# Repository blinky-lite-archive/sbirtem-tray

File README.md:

# SbirTem Thermal Imager
## .env file
`PROJECT=sbirtem`  
`DEVICETYPEA=sbirtem`  
`DEVICENAMEA=01`  
`MQTTCLIENTID=sbirtem-tray-01`  
`MQTTSERVERIP=`*your-MQTT-broker-URL*  
`MQTTUSERNAME=`*your-MQTT-broker-username*  
`MQTTPASSWORD=`*your-MQTT-broker-password*
`NODEREDCONFIGSECRET=`*another-choice*

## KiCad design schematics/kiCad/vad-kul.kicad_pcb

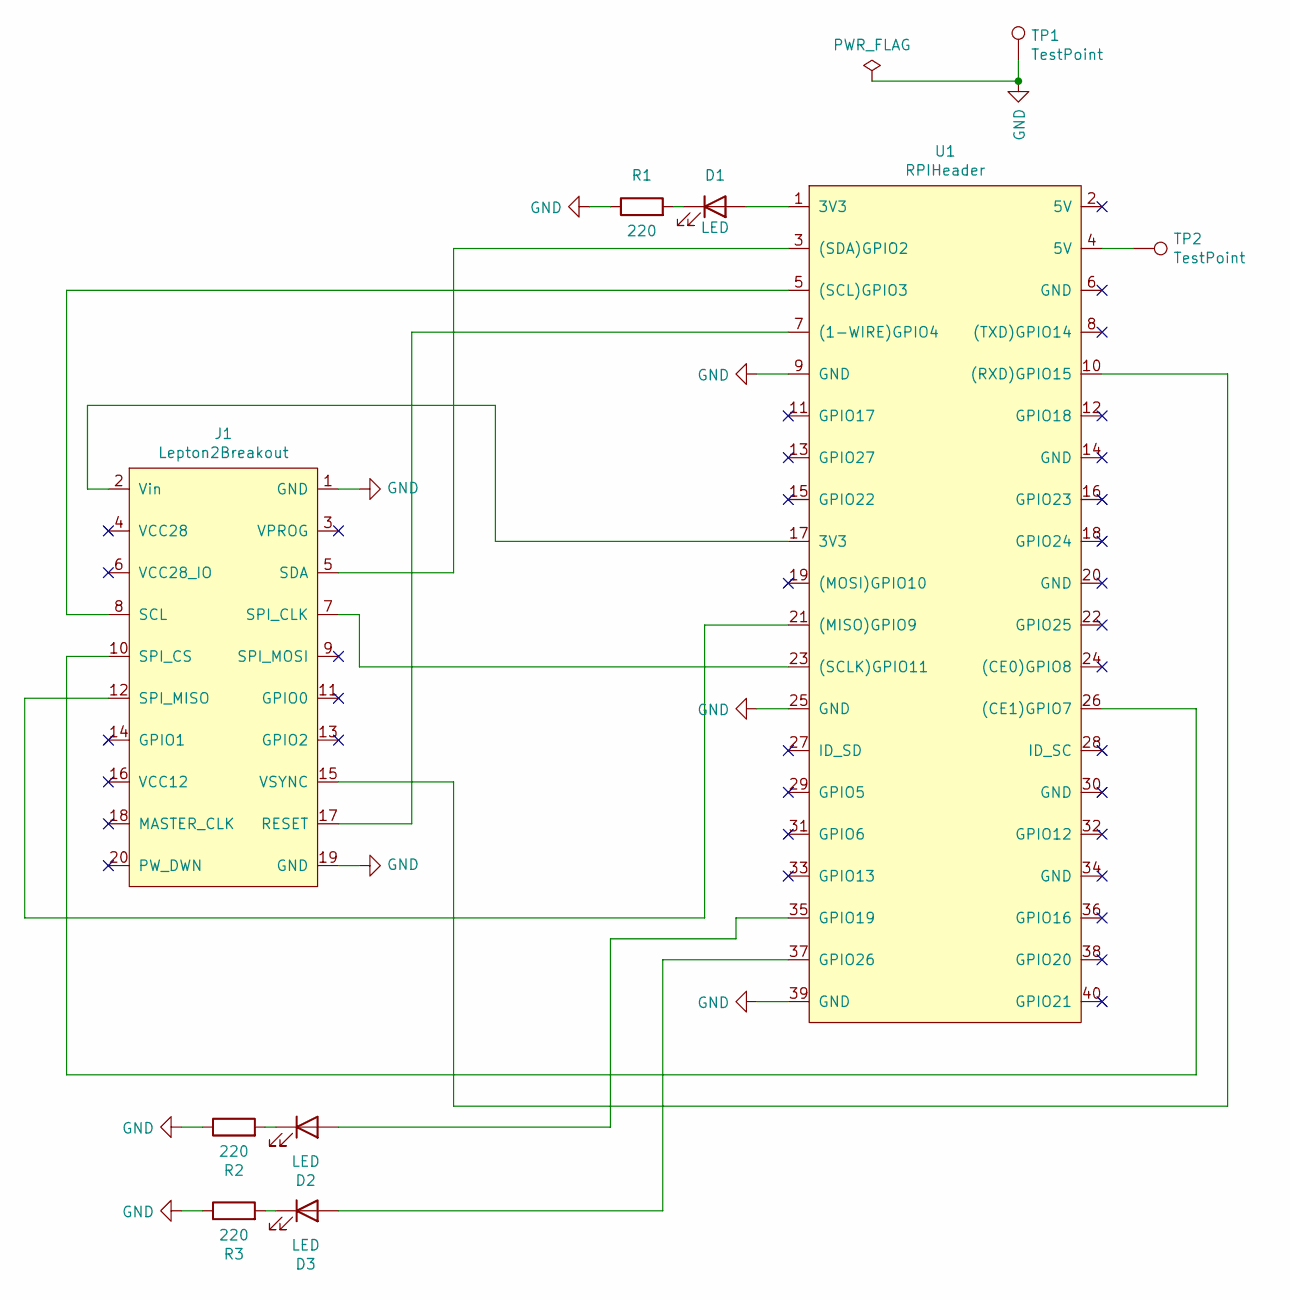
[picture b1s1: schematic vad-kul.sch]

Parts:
D1, D2, D3: LED; LED_D5.0mm
J1: Lepton2Breakout; Lepton2BO_RA
R1, R2, R3: 220; R_1206_3216Metric_Pad1.42x1.75mm_HandSolder
TP1, TP2: TestPoint; PinHeader_1x01_P2.54mm_Vertical
U1: RPIHeader; PinHeader_2x20_P2.54mm_Vertical

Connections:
GND: J1.1 (GND), J1.19 (GND), R1.1, R2.1, R3.1, TP1.1, U1.9 (GND), U1.25 (GND), U1.39 (GND)
unnamed: D1.1 (K), R1.2
unnamed: D1.2 (A), U1.1 (3V3)
unnamed: D2.1 (K), R2.2
unnamed: D2.2 (A), U1.35 (GPIO19)
unnamed: D3.1 (K), R3.2
unnamed: D3.2 (A), U1.37 (GPIO26)
unnamed: J1.2 (Vin), U1.17 (3V3)
unnamed: J1.5 (SDA), U1.3 ((SDA)GPIO2)
unnamed: J1.7 (SPI_CLK), U1.23 ((SCLK)GPIO11)
unnamed: J1.8 (SCL), U1.5 ((SCL)GPIO3)
unnamed: J1.10 (SPI_CS), U1.26 ((CE1)GPIO7)
unnamed: J1.12 (SPI_MISO), U1.21 ((MISO)GPIO9)
unnamed: J1.15 (VSYNC), U1.10 ((RXD)GPIO15)
unnamed: J1.17 (RESET), U1.7 ((1-WIRE)GPIO4)
unnamed: TP2.1, U1.4 (5V)

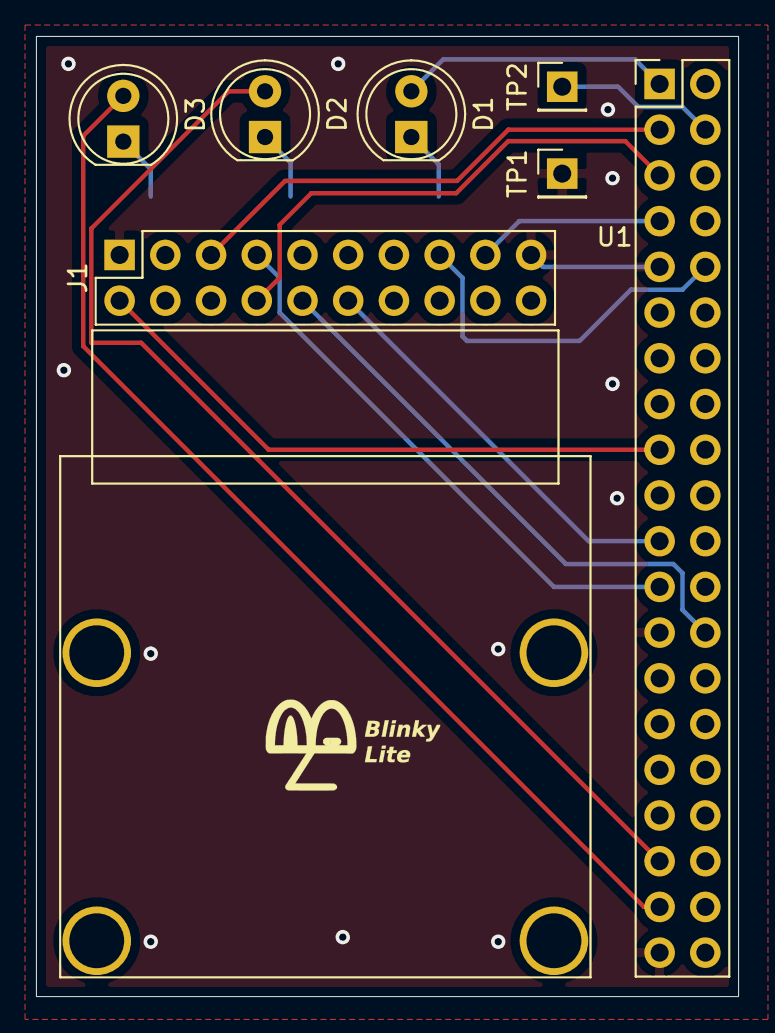
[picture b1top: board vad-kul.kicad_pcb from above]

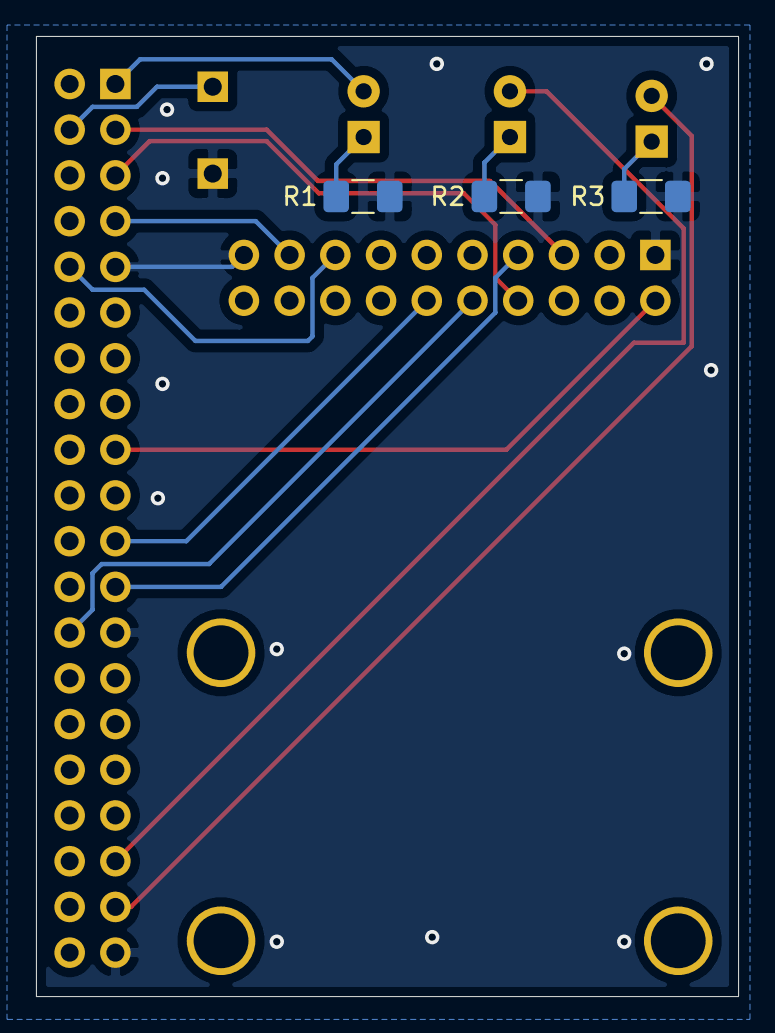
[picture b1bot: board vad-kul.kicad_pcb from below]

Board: 2 copper layers, 39.0 x 53.3 mm, 10 parts (3 on the bottom side), 16 nets.

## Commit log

2020-05-10 thermal sensor working
2020-05-11 spectoimage working
2020-05-12 auto scale toggle working
2020-05-12 updated delay time
2020-05-12 removed MQTT
2020-05-12 added calibration routine
2020-05-12 changed min max limits
2020-05-16 removed index app
2020-05-18 added image to readme
2020-05-21 using c program for image acq
2020-05-23 changed device name
2020-05-23 connected to MQTT
2020-05-24 added better kill and enhancmenet
2020-05-24 added wsreconnect
2020-05-24 fixed spelling error
2020-05-25 added take image button
2020-05-25 fixed json filter
2020-05-27 more formatting on README
2020-05-31 added Led control
2020-05-31 no init image on local
2020-05-31 clear image before taking
2020-05-31 bigger temp font
2020-06-05 changed tray name
2020-06-05 changed type in json
2020-06-05 changed init status LED to on
2020-06-11 added kicad schematics
2020-06-13 updated settings
2020-06-13 auto mode seems to be working
2020-06-14 pixel histogram, alarm, and themp thresh
2020-06-14 cleaned flow error check
2020-06-15 added auto reboot and alarm toggle
2020-06-15 blink red only if successful
2020-06-29 removed cube info and specific name for settings file
2020-06-29 added flip horz and vert
2020-06-29 history chart and loop delay change
2020-07-01 changed spi clock to 20 MHz
2020-07-01 settings for image cuts
2020-07-01 does not send image for mqtt
2020-07-02 added SR04 to schematic lib
2020-07-03 new pcb with sr04
2020-07-15 new circuit board with HCSR04
2020-07-15 changed setting name to 04
2020-07-20 switched wlan0 and wlan1
2020-08-04 removed jwt token
2020-08-11 wireless router setup finished
2020-08-27 removed setting i2c bus to zero
2020-08-27 added i2c code
2020-08-27 added more i2c routines
2020-08-27 added manual ffc
2020-09-12 before new branch
2020-09-12 new led prot
2020-09-14 simple screen update
2020-09-14 opto spi
2020-09-15 removed simple alarm web app
2020-09-15 added body temp
2020-09-17 put rounding in body temp
2020-09-21 removed yellow LED
2020-09-24 simple web app
2020-09-25 added display scoket
2020-09-25 added profile app to camera
2020-09-29 changed delay on mqtt to 2 secs
2020-09-29 added yellow blink when imager hangs
2020-09-30 added image bluring
2020-10-01 updated blur
2020-10-07 slowed down non image rate
2020-10-16 added drop down to blur and trigger mode
2020-10-19 all trig modes working
2020-10-19 removed horz par from expert plot
2020-10-19 cleanup init
2020-10-22 gate-mode
2020-10-23 put ellipse on local profile web app
2020-10-23 sleep profile fixed
2020-10-25 working gate and pattern area
2020-10-26 Swedish speak
2020-10-27 added filter on ultrasound
2020-10-28 different languages
2020-10-28 fixed threshold bug in manual mode
2020-10-29 comfort display blurred
2020-11-01 period mode runs profile
2020-11-04 ellipse area for compute
2020-11-04 added calib transient corr
2020-11-04 changed message rate limit
2020-11-08 working lepton3p5
2020-11-08 hi res buff trans working
2020-11-09 complete working hi res
2020-11-09 simplified display
2020-11-11 cleaned up flows and spi mode = 3
2020-11-11 added keep alive time
2020-11-11 added instructions
2020-11-11 settings for low res
2020-11-14 hi res offset fixed along with image sharp
2020-11-16 plasma color map
2020-11-17 rotated display
2020-11-17 fixed rotated screen launcher
2020-11-18 working hi res in 90 degree mode
2020-11-18 rudim facial rec and comp working
2020-11-20 tear duct search working
2020-11-21 switching to sbirtem
2020-11-21 sbirtem changeover complete
2020-11-21 circles for eye detect
2020-11-23 changed face threshhold to 0.6
2020-11-28 new face recog
2020-11-28 fixed action LEDs
2020-11-28 check on body temp eq 0
2020-11-30 changed ellipse size
2020-12-01 added ping
2020-12-01 added mqtt ping subscriber
2020-12-02 hard screen on off
2020-12-03 added peak hold
2020-12-04 wait meas count
2020-12-16 added wait comment
2020-12-17 added border, fixed language, removed gate, wireless setup
2021-01-06 before new screens
2021-01-07 new monitor screen
2021-01-08 changed colors
2021-01-09 added hold and alignment
2021-01-09 sped up acq
2021-01-09 orig settings
2021-01-09 added max count on outside range
2021-01-10 updated monitor layout
2021-11-08 simplified flow
2021-11-08 working sensor app
2021-11-08 added tap on screen
2021-11-10 put external monitor
2021-11-11 new sequenc
2021-11-12 stopseq fixed
2021-11-12 app scaling working
2021-11-12 changed out of range background color
2021-11-12 start of boo boo bunny
2021-11-13 latest
2021-11-13 low failure rate
2021-11-13 working temp system again
2021-11-13 fixed camera process at init
2021-11-13 added variable averages
2021-11-13 all working
2021-11-14 switched to Demo 02 and updated capture35
2021-11-14 cosmetic to flirLepton35capture.c
